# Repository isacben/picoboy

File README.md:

# picoboy

Alpha version of a handheld console for PICO-8 games that runs on a Raspberry Pi Zero W.

# Bill Of Materials

| Symbol | Description | Reference part | Value | Price (USD) |
| --- | --- | --- | --- | --- |
| - | Game Boy Color shell (with accessories) | [Amazon](https://www.amazon.com/dp/B09HH5B6PB) | - | $20.66 |
| - | Raspberry Pi charger | [Adafruit](https://www.adafruit.com/product/1995) | - | $8.25 |
| ? | Raspberry Pi Zero 2 W | [Adafruit](https://www.adafruit.com/product/5291) | - | $16.00 | |
| ? | Display | [Adafruit](https://www.adafruit.com/product/1774) | 2.8 inch | $14.95 |
| U6 | Audio Amplifier | [LM4875M/NOPB](https://www.digikey.com/en/products/detail/texas-instruments/lm4875m-nopb/1871687) | 2.7V ~ 5.5V | $2.32 |
| R17 | Potentiometer (volume) | [3352T-1-253LF](https://www.digikey.com/en/products/detail/bourns-inc/3352T-1-253LF/1088348) | 25 kOhms | $2.50 |
| R18 | Resistor | [NFR2500001500JR500](https://www.digikey.com/en/products/detail/vishay-beyschlag-draloric-bc-components/NFR2500001500JR500/614093) | 150 Ohms | $0.38|
| R19 | Resistor | [CFR25J100K](https://www.digikey.com/en/products/detail/te-connectivity-passive-product/CFR25J100K/2380563) | 100 kOhms | $0.10 |
| C7 | Capacitor | [K221J15C0GF5TL2](https://www.digikey.com/en/products/detail/vishay-beyschlag-draloric-bc-components/K221J15C0GF5TL2/286471) | 220pF | $0.26 |
| C7 | Capacitor |  | 0.22uF | ? |
| C8 | Capacitor | [FG28X5R1H105KRT06](https://www.digikey.com/en/products/detail/tdk-corporation/FG28X5R1H105KRT06/5803193) | 1uF | $0.35 |
| C9 | Capacitor | [FG28X5R1H105KRT06](https://www.digikey.com/en/products/detail/tdk-corporation/FG28X5R1H105KRT06/5803193) | 1uF | $0.35 |
| C10 | Capacitor | [TD100M6.3](https://www.digikey.com/en/products/detail/nte-electronics-inc/TD100M6-3/11650229) | 100uF | $2.84 |
| J1 | Audio Jack | [SJ1-3525NG-GR](https://www.digikey.com/en/products/detail/cui-devices/SJ1-3525NG-GR/2295990) | - | $0.85 |
| J2 | Speaker | [Handheld Legend](https://handheldlegend.com/products/game-boy-color-pocket-clear-speaker-funnyplaying?_pos=1&_sid=534442f70&_ss=r) | 8 Ohms | $3.99 |

## SMD components

| Symbol | Description | Reference part | Value | Price (USD) |
| --- | --- | --- | --- | --- |
| R18 | Resistor | [ERJ-PA3J151V](https://www.digikey.com/en/products/detail/panasonic-electronic-components/ERJ-PA3J151V/5035990) | 150 Ohms | $0.11|
| R19 | Resistor | [ERJ-PA3J104V](https://www.digikey.com/en/products/detail/panasonic-electronic-components/ERJ-PA3J104V/5035972) | 100 kOhms | $0.11 |
| C7 | Capacitor | [CL10A226MP8NUNE](https://www.digikey.com/en/products/detail/samsung-electro-mechanics/CL10A226MP8NUNE/3886932) | 0.22uF | $0.18 |
| C8 | Capacitor | [CL10A105KP8NNC](https://www.digikey.com/en/products/detail/samsung-electro-mechanics/CL10A105KP8NNNC/3886840) | 1uF | $0.10 |
| C9 | Capacitor | [CL10A105KP8NNC](https://www.digikey.com/en/products/detail/samsung-electro-mechanics/CL10A105KP8NNNC/3886840) | 1uF | $0.10 |
| C10 | Capacitor | [T520A107M006ATE070](https://www.digikey.com/en/products/detail/kemet/T520A107M006ATE070/4246283) | 100uF | $0.94 |

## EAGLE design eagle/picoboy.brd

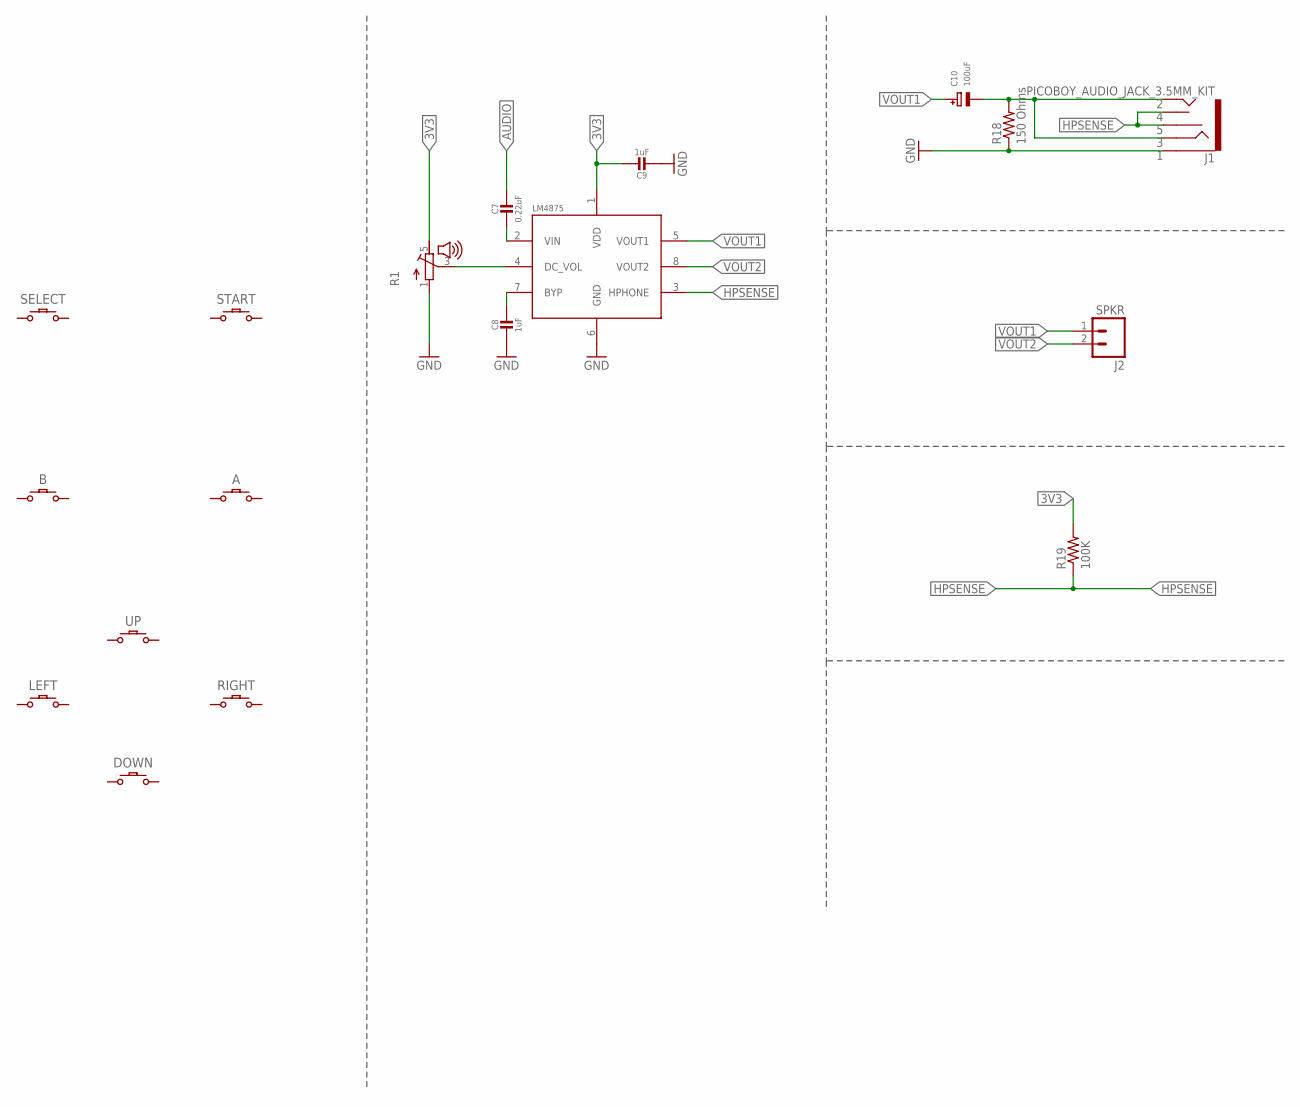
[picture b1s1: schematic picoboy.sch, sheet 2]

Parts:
A: PICOBOY_CONDUCTIVE_BUTTONCONDUCTIVE_BUTTON_THICK; PICOBOY_CONDUCTIVE_BUTTON_THICK
B: PICOBOY_CONDUCTIVE_BUTTONCONDUCTIVE_BUTTON_THICK; PICOBOY_CONDUCTIVE_BUTTON_THICK
C7: 0.22uF; PICOBOY_CAPACITOR_0603-MINI
C8, C9: 1uF; PICOBOY_CAPACITOR_0603-MINI
C10: 100uF; PICOBOY_CAPACITOR_EIA3216-18/A-W
DOWN: PICOBOY_CONDUCTIVE_BUTTONCONDUCTIVE_BUTTON_DIRECT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; PICOBOY_CONDUCTIVE_BUTTON_DIRECTIONAL_THICK
J1: PICOBOY_AUDIO_JACK_3.5MM_KIT; PICOBOY_AUDIO-JACK-KIT
J2: SPKR; 02P
LEFT: PICOBOY_CONDUCTIVE_BUTTONCONDUCTIVE_BUTTON_DIRECT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; PICOBOY_CONDUCTIVE_BUTTON_DIRECTIONAL_THICK
LM4875: PICOBOY_LM4875
R1: PICOBOY_VOLUME_WHEEL
R18: 150 Ohms; R0603
R19: 100K; R0603
RIGHT: PICOBOY_CONDUCTIVE_BUTTONCONDUCTIVE_BUTTON_DIRECT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; PICOBOY_CONDUCTIVE_BUTTON_DIRECTIONAL_THICK
SELECT: PICOBOY_CONDUCTIVE_BUTTON_STARTSELECTCONDUCTIVE_B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; PICOBOY_CONDUCTIVE_BUTTON_THICK_STARTSELECT
START: PICOBOY_CONDUCTIVE_BUTTON_STARTSELECTCONDUCTIVE_B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; PICOBOY_CONDUCTIVE_BUTTON_THICK_STARTSELECT
UP: PICOBOY_CONDUCTIVE_BUTTONCONDUCTIVE_BUTTON_DIRECT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; PICOBOY_CONDUCTIVE_BUTTON_DIRECTIONAL_THICK

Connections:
3V3: C9.1, LM4875.1 (VDD), R1.5 (E), R19.2
AUDIO: C7.1
BYP: C8.1, LM4875.7 (BYP)
DC_VOL: LM4875.4 (DC_VOL), R1.3 (S)
GND: C8.2, C9.2, J1.SLEEVE, LM4875.6 (GND), R1.1 (A), R18.1
HPSENSE: J1.RSH, J1.TSH, LM4875.3 (HPHONE), R19.1
unnamed: C10.-, J1.RING, J1.TIP, R18.2
VIN: C7.2, LM4875.2 (VIN)
VOUT1: C10.+, J2.1, LM4875.5 (VOUT1)
VOUT2: J2.2, LM4875.8 (VOUT2)

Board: 2 copper layers, 19 parts (0 on the bottom side), 9 nets, no tracks yet.

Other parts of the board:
U$1: PICOBOY_GBC_BOARD_OUTLINE

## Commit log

2023-03-29 Add .gitignore
2023-03-29 Add eagle files
2023-03-30 Update buttons possition on PCB
2023-04-08 Add bill of materials
2023-04-08 Update bill of materials
2023-04-13 Add components to the BOM
2023-04-14 Add capacitors to the BOM
2023-04-18 Started eagle library
2023-04-19 Update holes dimensions
2023-04-22 Update holes position on PCB
2023-04-22 Update PCB size
2023-04-27 Replace Game Boy Pocket with Game Boy Color PCB outline
2023-04-28 Added devices to library
2023-04-29 Add SMD components for the audio amp
2023-04-29 Add auidio amp devices to eagle lib
2023-05-03 Start amplifier schematics
2023-05-06 Wired all audio components
